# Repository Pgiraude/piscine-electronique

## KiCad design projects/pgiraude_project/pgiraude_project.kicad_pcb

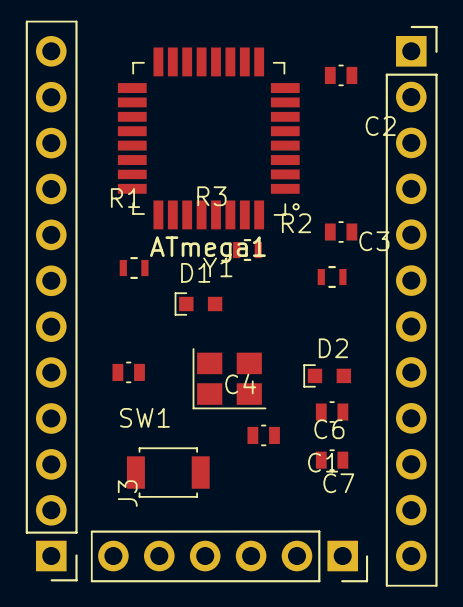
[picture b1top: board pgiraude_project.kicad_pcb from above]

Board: 2 copper layers, 17 parts (0 on the bottom side), 30 nets, no tracks yet.

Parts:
ATmega1: ATmega328-PAU
C1, C2: 12pF; capacitor
C3, C4, C7: 100nF; capacitor
C6: 1uF; capacitor
D1: Green; led
D2: Red; led
J1: connector_1
J2: connector_2
J3: connector_3
R1: 330; Resistor
R2: Resistor
R3: 10K; Resistor
SW1: SW_Push; switch
Y1: 16MHz; Crystal

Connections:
A0: ATmega1.23 (PC0), J2.8 (A0)
A1: ATmega1.24 (PC1), J2.7 (A1)
A2: ATmega1.25 (PC2), J2.6 (A2)
A3: ATmega1.26 (PC3), J2.5 (A3)
D2: ATmega1.32 (PD2), J1.8 (D2)
D3: ATmega1.1 (PD3), J1.7 (D3)
D4: ATmega1.2 (PD4), J1.6 (D4)
D5: ATmega1.9 (PD5), J1.5 (D5)
D6: ATmega1.10 (PD6), J1.4 (D6)
D7: ATmega1.11 (PD7), J1.3 (D7)
D8: ATmega1.12 (PB0), J1.2 (D8)
D9: ATmega1.13 (PB1), J1.1 (D9)
D10: ATmega1.14 (PB2), J2.12 (D10)
DTR: ATmega1.29 (RESET/PC6), J1.10 (RST), J2.3 (RST), J3.1 (DTR), R3.2, SW1.2
GND: J1.9 (GND), J2.2 (GND), J3.5 (GND), J3.6 (GND)
MISO: ATmega1.16 (PB4), J2.10 (MISO)
MOSI: ATmega1.15 (PB3), J2.11 (MOSI)
unnamed: ATmega1.20 (AREF), C3.2
unnamed: ATmega1.4 (VCC), ATmega1.18 (AVCC)
unnamed: ATmega1.7 (XTAL1/PB6), C2.1, Y1.1
unnamed: ATmega1.8 (XTAL2/PB7), C1.1, Y1.3
unnamed: C1.2, C2.2, Y1.2
unnamed: C4.2, SW1.1
unnamed: D1.2 (A), R1.2
unnamed: D2.1 (K), R2.1
RAW: C6.1, C7.1, D2.2 (A), J2.1 (RAW)
RXI: ATmega1.30 (PD0), J1.11 (RXI), J3.3 (RXI)
SCK: ATmega1.17 (PB5), J2.9 (SCK), R1.1
TXO: ATmega1.31 (PD1), J1.12 (TXO), J3.2 (TXO)
VCC: J2.4 (VCC), J3.4 (VCC)

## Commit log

2025-11-19 docker compose kicad
2025-11-19 save config setup
2025-11-19 fix path
2025-11-21 add atmega328P-A symbol
2025-11-22 footprint
2025-11-24 foot print
2025-11-26 pcb editor
2025-11-26 last
2025-11-27 final
